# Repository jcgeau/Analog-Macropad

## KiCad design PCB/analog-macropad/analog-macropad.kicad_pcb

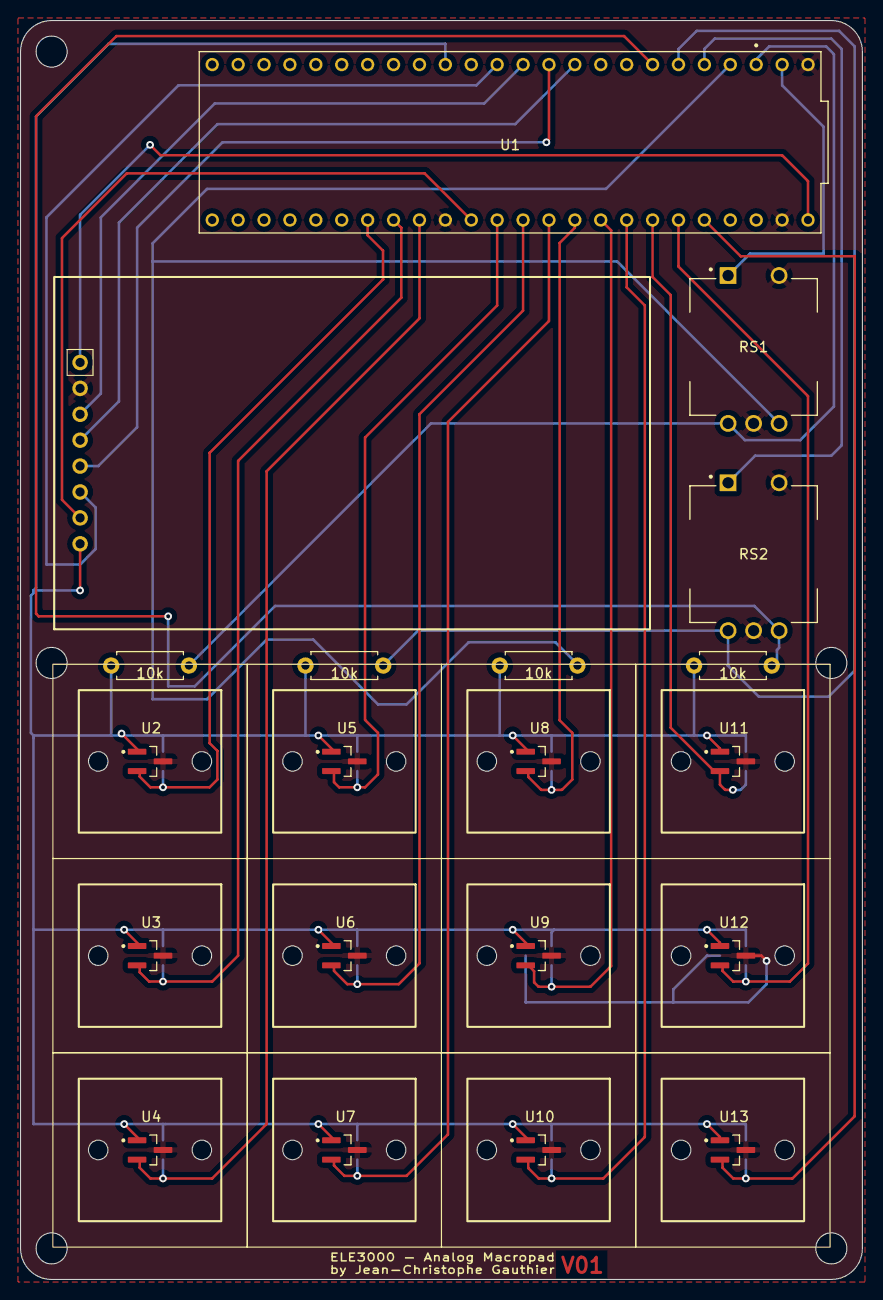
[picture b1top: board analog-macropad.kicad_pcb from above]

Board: 2 copper layers, 82.5 x 123.4 mm, 20 parts (0 on the bottom side), 26 nets.

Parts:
10k, 10k#2, 10k#3, 10k#4: 10k; R_Axial_DIN0207_L6.3mm_D2.5mm_P7.62mm_Horizontal
RS1, RS2: rotary encoder
U1: Teensy 4.1
U2, U3, U4, U5, U6, U7, U8, U9, U10, U11, U12, U13: hall-effect sensor; hall sensor
U14: ST7735

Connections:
3.3V: 10k.2, 10k#2.2, 10k#3.2, 10k#4.2, U1.3.3V_1 (3.3V), U2.1 (VCC), U3.1 (VCC), U4.1 (VCC), U5.1 (VCC), U6.1 (VCC), U7.1 (VCC), U8.1 (VCC), U9.1 (VCC), U10.1 (VCC), U11.1 (VCC), U12.1 (VCC), U13.1 (VCC), U14.8 (LED)
5V: U1.VIN, U14.1 (VCC)
A0: U1.14 (A0), U5.2 (VOUT)
A1: U1.15 (A1), U6.2 (VOUT)
A2: U1.16 (A2), U7.2 (VOUT)
A3: U1.17 (A3), U8.2 (VOUT)
A4: U1.18 (A4), U9.2 (VOUT)
A5: U1.19 (A5), U10.2 (VOUT)
A6: U1.20 (A6), U11.2 (VOUT)
A7: U1.21 (A7), U12.2 (VOUT)
A8: U1.22 (A8), U13.2 (VOUT)
A15: U1.39 (A15), U2.2 (VOUT)
A16: U1.40 (A16), U3.2 (VOUT)
A17: U1.41 (A17), U4.2 (VOUT)
CLK1: 10k#2.1, RS1.1 (A), U1.1 (TX1)
CLK2: 10k#3.1, RS2.1 (A), U1.4 (BCLK2)
CS: U1.10 (CS1), U14.3 (CS_U1)
DC: U1.9 (OUT1C), U14.5 (AO)
DT1: 10k.1, RS1.3 (B), U1.2 (OUT2)
DT2: 10k#4.1, RS2.3 (B), U1.5 (IN2)
GND: RS1.2 (C), RS1.5 (S2), RS2.2 (C), RS2.5 (S2), U1.GND1 (GND), U1.GND2 (GND), U1.GND3 (GND), U2.3 (GND), U3.3 (GND), U4.3 (GND), U5.3 (GND), U6.3 (GND), U7.3 (GND), U8.3 (GND), U9.3 (GND), U10.3 (GND), U11.3 (GND), U12.3 (GND), U13.3 (GND), U14.2 (GND)
RST: U1.8 (TX2), U14.4 (RESET)
SCK: U1.13 (SCK), U14.7 (SCK)
SDA: U1.11 (MOSI), U14.6 (SDA)
SW1: RS1.4 (S1), U1.0 (RX1)
SW2: RS2.4 (S1), U1.3 (LRCLK2)

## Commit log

2024-05-16 setup du repo
2024-05-16 déclaration des classes AnalogKey et AnalogKeyboard
2024-05-16 ajustement des fichiers
2024-05-16 continuation du code implémentation de quelques méthodes
2024-05-24 reformulation du code pour utiliser une autre library que Keyboard
2024-05-27 creation des fcts read write et print de keayboard
2024-05-29 travail sur le main
2024-05-29 trying to compile code
2024-06-18 version fonctionnel de une touche
2024-06-19 creation du fichier constants.h qui fonctionne
2024-07-09 refacturing
2024-07-10 création du projet pcb et l'implémentation des macros fonctionnent
2024-07-11 finit le circuit design presque pret a commencer le pcb
2024-07-17 pcb finit pret a commander
2024-07-24 pcb commandé avec quelques changements au code
2024-07-28 implémentation de la classe encoder
2024-07-29 création de la classe screen pour gérer l'interface usager
2024-07-31 Implémentation des fonctions tests pour faciliter le test de chaque composantes
2024-08-04 quasi fin de la fonction run et implémentation de l'affichage en mode veille
2024-08-06 debug de la classe rotary encoder
2024-08-06 clavier completement fonctionnel
2024-08-08 Documentation de *pratiquement* tout le code
2024-08-12 changements
2024-08-16 changements effectué pour la préparation à la présentation du projet
2024-12-23 changement du constant
